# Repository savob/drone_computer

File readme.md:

# Flight Computer Project

This is the code and hardware design files for my custom flight computer board and its components.

It's been on a haitus for a while, I hope to pick it up again sometime though.

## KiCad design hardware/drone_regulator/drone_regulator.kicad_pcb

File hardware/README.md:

# Flight Computer Hardware Files

Here are the files related to the hardware design. They are all from KiCad 7.0.10 at the oldest.

## Projects

| Project | Description |
| --- | --- |
| `drone_regulator` | An noise rejecting voltage regulator board |
| `flight_computer_vX` | Different versions of the flight computer |

## Other Files and Folders

| Folder | Purpose |
| --- | --- |
| `renders` | Front and back 3D renders of the boards |
| `schematics` | Has the schematics in PDF (colour and B/W) and SVG (just colour) formats |
| `small_title_block.kicad_wks` | has the worksheet template with a more compact titleblock |

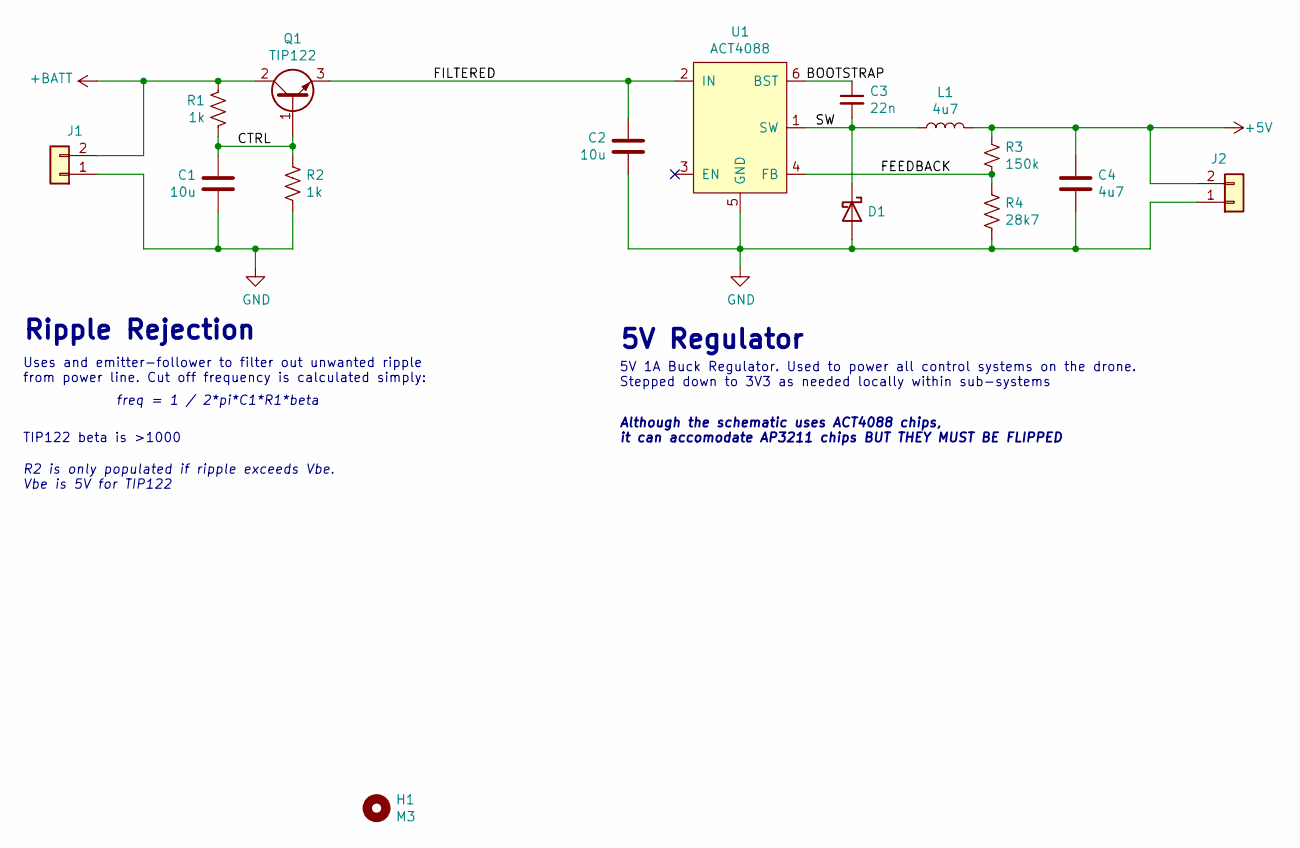
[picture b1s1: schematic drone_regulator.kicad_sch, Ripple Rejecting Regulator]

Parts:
C1: 10u; C_Radial_D6.3mm_H7.0mm_P2.50mm
C2: 10u; C_0805_2012Metric
C3: 22n; C_0402_1005Metric
C4: 4u7; C_0805_2012Metric
D1: 0v7; D_SOD-323
H1: M3; MountingHole_3.2mm_M3
J1, J2: Conn_01x02; PinHeader_1x02_P2.54mm_Vertical
L1: 4u7; L_Taiyo-Yuden_NR-30xx
Q1: TIP122; TO-220-3_Vertical
R1, R2: 1k; R_Axial_DIN0207_L6.3mm_D2.5mm_P2.54mm_Vertical
R3: 150k; R_0402_1005Metric
R4: 28k7; R_0402_1005Metric
U1: ACT4088; SOT-23-6

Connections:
+5V: C4.1, J2.2, L1.2, R3.1
+BATT: J1.2, Q1.2 (C), R1.2
/BOOTSTRAP: C3.1, U1.6 (BST)
/CTRL: C1.2, Q1.1 (B), R1.1, R2.2
/FEEDBACK: R3.2, R4.1, U1.4 (FB)
/FILTERED: C2.2, Q1.3 (E), U1.2 (IN)
/SW: C3.2, D1.1 (K), L1.1, U1.1 (SW)
GND: C1.1, C2.1, C4.2, D1.2 (A), J1.1, J2.1, R2.1, R4.2, U1.5 (GND)

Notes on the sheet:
5V 1A Buck Regulator. Used to power all control systems on the drone. Stepped down to 3V3 as needed locally within sub-systems
R2 is only populated if ripple exceeds Vbe. Vbe is 5V for TIP122
Ripple Rejection
Although the schematic uses ACT4088 chips, it can accomodate AP3211 chips BUT THEY MUST BE FLIPPED
Uses and emitter-follower to filter out unwanted ripple from power line. Cut off frequency is calculated simply: TIP122 beta is >1000
5V Regulator
freq = 1 / 2*pi*C1*R1*beta

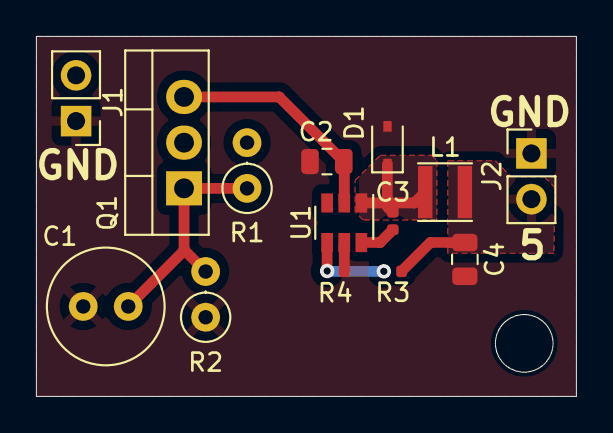
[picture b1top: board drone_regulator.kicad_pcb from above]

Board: 2 copper layers, 30.0 x 20.0 mm, 15 parts (0 on the bottom side), 8 nets.

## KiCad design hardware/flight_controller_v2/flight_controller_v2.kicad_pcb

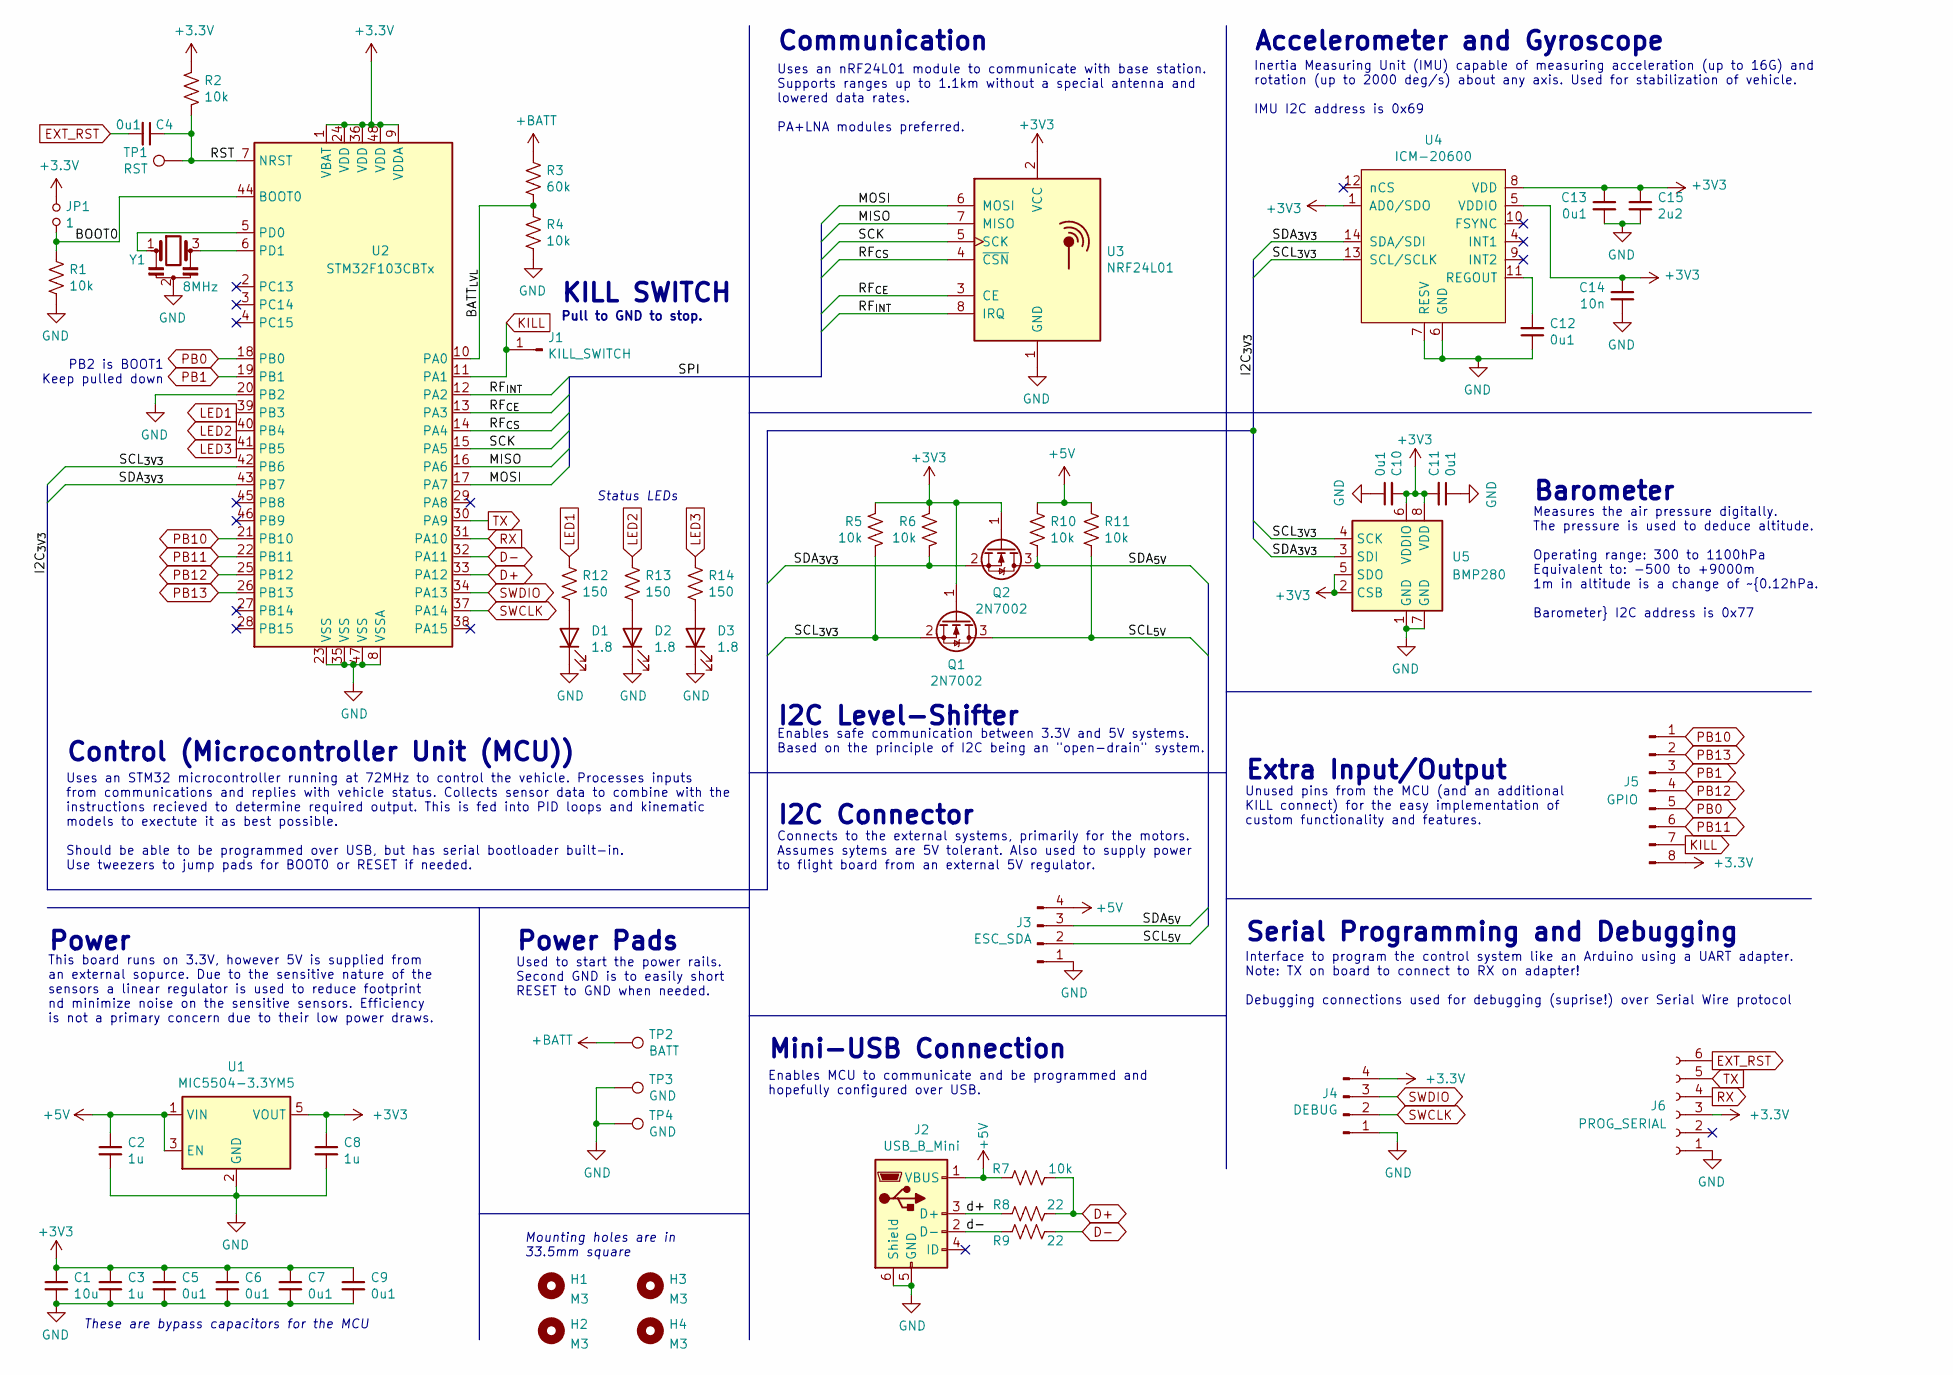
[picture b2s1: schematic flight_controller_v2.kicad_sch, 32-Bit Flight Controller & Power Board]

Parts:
C1: 10u; C_0603_1608Metric
C2, C3, C8: 1u; C_0603_1608Metric
C4, C5, C6, C7, C9, C10, C11, C12, C13: 0u1; C_0603_1608Metric
C14: 10n; C_0603_1608Metric
C15: 2u2; C_0603_1608Metric
D1, D2, D3: 1.8; LED_0805_2012Metric_Castellated
H1, H2, H3, H4: M3; MountingHole_3.2mm_M3
J1: KILL_SWITCH; PinHeader_1x01_P2.54mm_Vertical
J2: USB_B_Mini; TE_2172034-1
J3: ESC_SDA; PinHeader_1x04_P2.54mm_Vertical
J4: DEBUG; PinHeader_1x04_P2.54mm_Vertical
J5: GPIO; PinHeader_2x04_P2.00mm_Vertical_SMD
J6: PROG_SERIAL; PinSocket_1x06_P2.54mm_Vertical
JP1: 1; SolderJumper-2_P1.3mm_Open_Pad1.0x1.5mm
Q1, Q2: 2N7002; SOT-23
R1, R2, R4, R5, R6, R7, R10, R11: 10k; R_0603_1608Metric
R3: 60k; R_0603_1608Metric
R8, R9: 22; R_0603_1608Metric
R12, R13, R14: 150; R_0603_1608Metric
TP1: RST; TestPoint_Pad_1.5x1.5mm
TP2: BATT; TestPoint_Pad_4.0x4.0mm
TP3: GND; TestPoint_Pad_D2.0mm
TP4: GND; TestPoint_Pad_4.0x4.0mm
U1: MIC5504-3.3YM5; SOT-23-5
U2: STM32F103CBTx; LQFP-48_7x7mm_P0.5mm
U3: NRF24L01; nRF24L01_Breakout
U4: ICM-20600; LGA-14_3x2.5mm_P0.5mm_LayoutBorder3x4y
U5: BMP280; Bosch_LGA-8_2x2.5mm_P0.65mm_ClockwisePinNumbering
Y1: 8MHz; Resonator_SMD_muRata_CSTxExxV-3Pin_3.0x1.1mm

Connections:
+5V: C2.1, J2.1 (VBUS), J3.4, R7.1, R10.1, R11.1, U1.1 (VIN), U1.3 (EN)
+BATT: R3.1, TP2.1
/BATT_{LVL}: R3.2, R4.1, U2.10 (PA0)
/BOOT0: JP1.1, R1.1, U2.44 (BOOT0)
/MISO: U2.16 (PA6), U3.7 (MISO)
/MOSI: U2.17 (PA7), U3.6 (MOSI)
/RF_{CE}: U2.13 (PA3), U3.3 (CE)
/RF_{CS}: U2.14 (PA4), U3.4 (~CSN)
/RF_{INT}: U2.12 (PA2), U3.8 (IRQ)
/RST: C4.1, R2.2, TP1.1, U2.7 (NRST)
/SCK: U2.15 (PA5), U3.5 (SCK)
/SCL_{3V3}: Q1.2 (S), R5.2, U2.42 (PB6), U4.13 (SCL/SCLK), U5.4 (SCK)
/SCL_{5V}: J3.2, Q1.3 (D), R11.2
/SDA_{3V3}: Q2.2 (S), R6.2, U2.43 (PB7), U4.14 (SDA/SDI), U5.3 (SDI)
/SDA_{5V}: J3.3, Q2.3 (D), R10.2
/d+: J2.3 (D+), R8.2
/d-: J2.2 (D-), R9.1
D+: R7.2, R8.1, U2.33 (PA12)
D-: R9.2, U2.32 (PA11)
EXT_RST: C4.2, J6.6
GND: C1.2, C2.2, C3.2, C5.2, C6.2, C7.2, C8.2, C9.2, C10.1, C11.1, C12.1, C13.2, C14.2, C15.2, D1.1 (K), D2.1 (K), D3.1 (K), J2.5 (GND), J2.6 (Shield), J3.1, J4.1, J6.1, R1.2, R4.2, TP3.1, TP4.1, U1.2 (GND), U2.8 (VSSA), U2.20 (PB2), U2.23 (VSS), U2.35 (VSS), U2.47 (VSS), U3.1 (GND), U4.6 (GND), U4.7 (RESV), U5.1 (GND), U5.7 (GND), Y1.2
KILL: J1.1, J5.7, U2.11 (PA1)
LED1: R12.1, U2.39 (PB3)
LED2: R13.1, U2.40 (PB4)
LED3: R14.1, U2.41 (PB5)
unnamed: C12.2, U4.11 (REGOUT)
unnamed: D1.2 (A), R12.2
unnamed: D2.2 (A), R13.2
unnamed: D3.2 (A), R14.2
unnamed: U2.5 (PD0), Y1.1
unnamed: U2.6 (PD1), Y1.3
PB0: J5.5, U2.18 (PB0)
PB1: J5.3, U2.19 (PB1)
PB10: J5.1, U2.21 (PB10)
PB11: J5.6, U2.22 (PB11)
PB12: J5.4, U2.25 (PB12)
PB13: J5.2, U2.26 (PB13)
RX: J6.4, U2.31 (PA10)
SWCLK: J4.2, U2.37 (PA14)
SWDIO: J4.3, U2.34 (PA13)
TX: J6.5, U2.30 (PA9)

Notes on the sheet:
Accelerometer and Gyroscope
This board runs on 3.3V, however 5V is supplied from an external sopurce. Due to the sensitive nature of the sensors a linear regulator is used to reduce footprint nd minimize noise on the sensitive sensors. Efficiency is not a primary concern due to their low power draws.
Barometer
Power
Extra Input/Output
I2C Level-Shifter
Enables safe communication between 3.3V and 5V systems. Based on the principle of I2C being an "open-drain" system.
I2C Connector
Pull to GND to stop.
Interface to program the control system like an Arduino using a UART adapter. Note: TX on board to connect to RX on adapter! Debugging connections used for debugging (suprise!) over Serial Wire protocol
Status LEDs
Used to start the power rails. Second GND is to easily short RESET to GND when needed.
Uses an nRF24L01 module to communicate with base station. Supports ranges up to 1.1km without a special antenna and lowered data rates. PA+LNA modules preferred.
Mounting holes are in 33.5mm square
Power Pads
Control (Microcontroller Unit (MCU))
Serial Programming and Debugging
PB2 is BOOT1 Keep pulled down
Inertia Measuring Unit (IMU) capable of measuring acceleration (up to 16G) and rotation (up to 2000 deg/s) about any axis. Used for stabilization of vehicle. IMU I2C address is 0x69
Mini-USB Connection
Communication
KILL SWITCH
Uses an STM32 microcontroller running at 72MHz to control the vehicle. Processes inputs from communications and replies with vehicle status. Collects sensor data to combine with the instructions recieved to determine required output. This is fed into PID loops and kinematic models to exectute it as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
Enables MCU to communicate and be programmed and hopefully configured over USB.
Connects to the external systems, primarily for the motors. Assumes sytems are 5V tolerant. Also used to supply power to flight board from an external 5V regulator.
These are bypass capacitors for the MCU
Unused pins from the MCU (and an additional KILL connect) for the easy implementation of custom functionality and features.
Measures the air pressure digitally. The pressure is used to deduce altitude. Operating range: 300 to 1100hPa Equivalent to: -500 to +9000m 1m in altitude is a change of ~{0.12hPa. Barometer} I2C address is 0x77

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
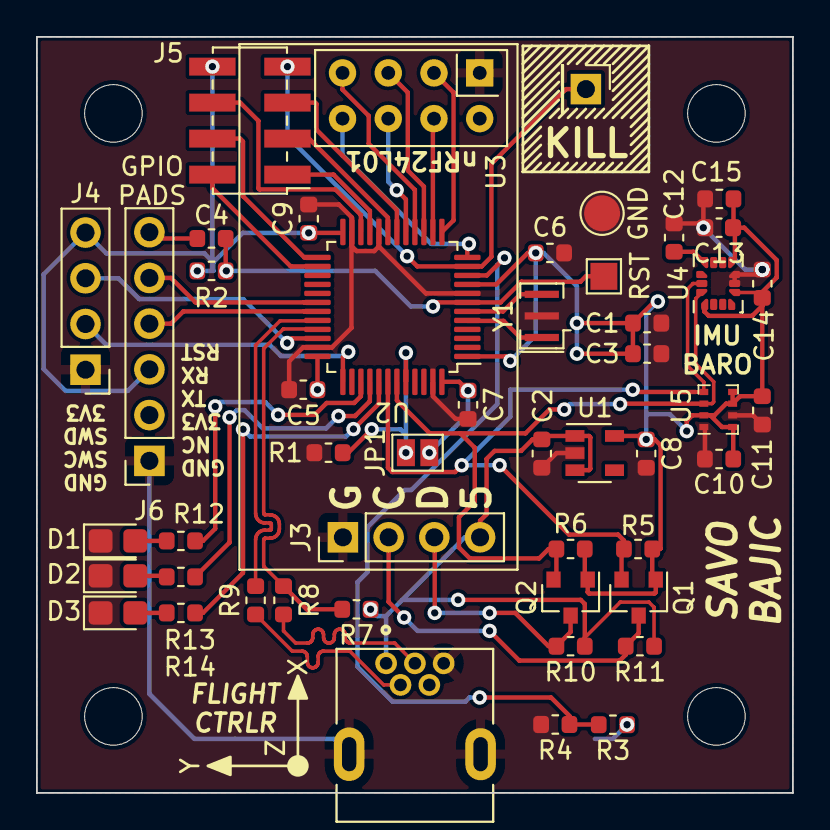
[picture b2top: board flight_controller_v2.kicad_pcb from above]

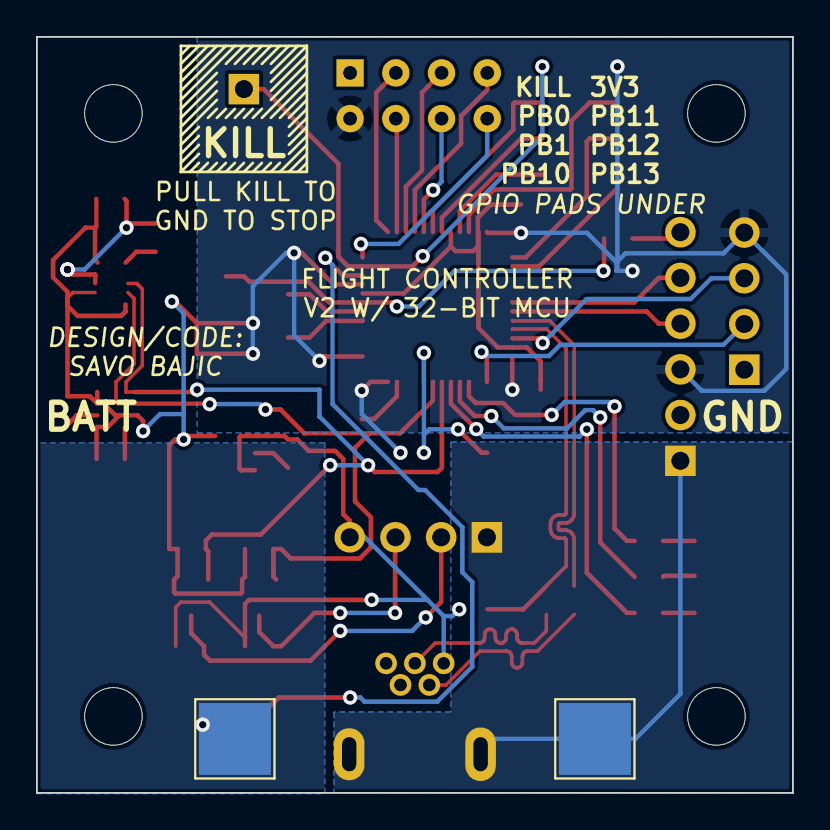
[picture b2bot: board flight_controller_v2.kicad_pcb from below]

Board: 2 copper layers, 42.0 x 42.0 mm, 55 parts (2 on the bottom side), 42 nets.

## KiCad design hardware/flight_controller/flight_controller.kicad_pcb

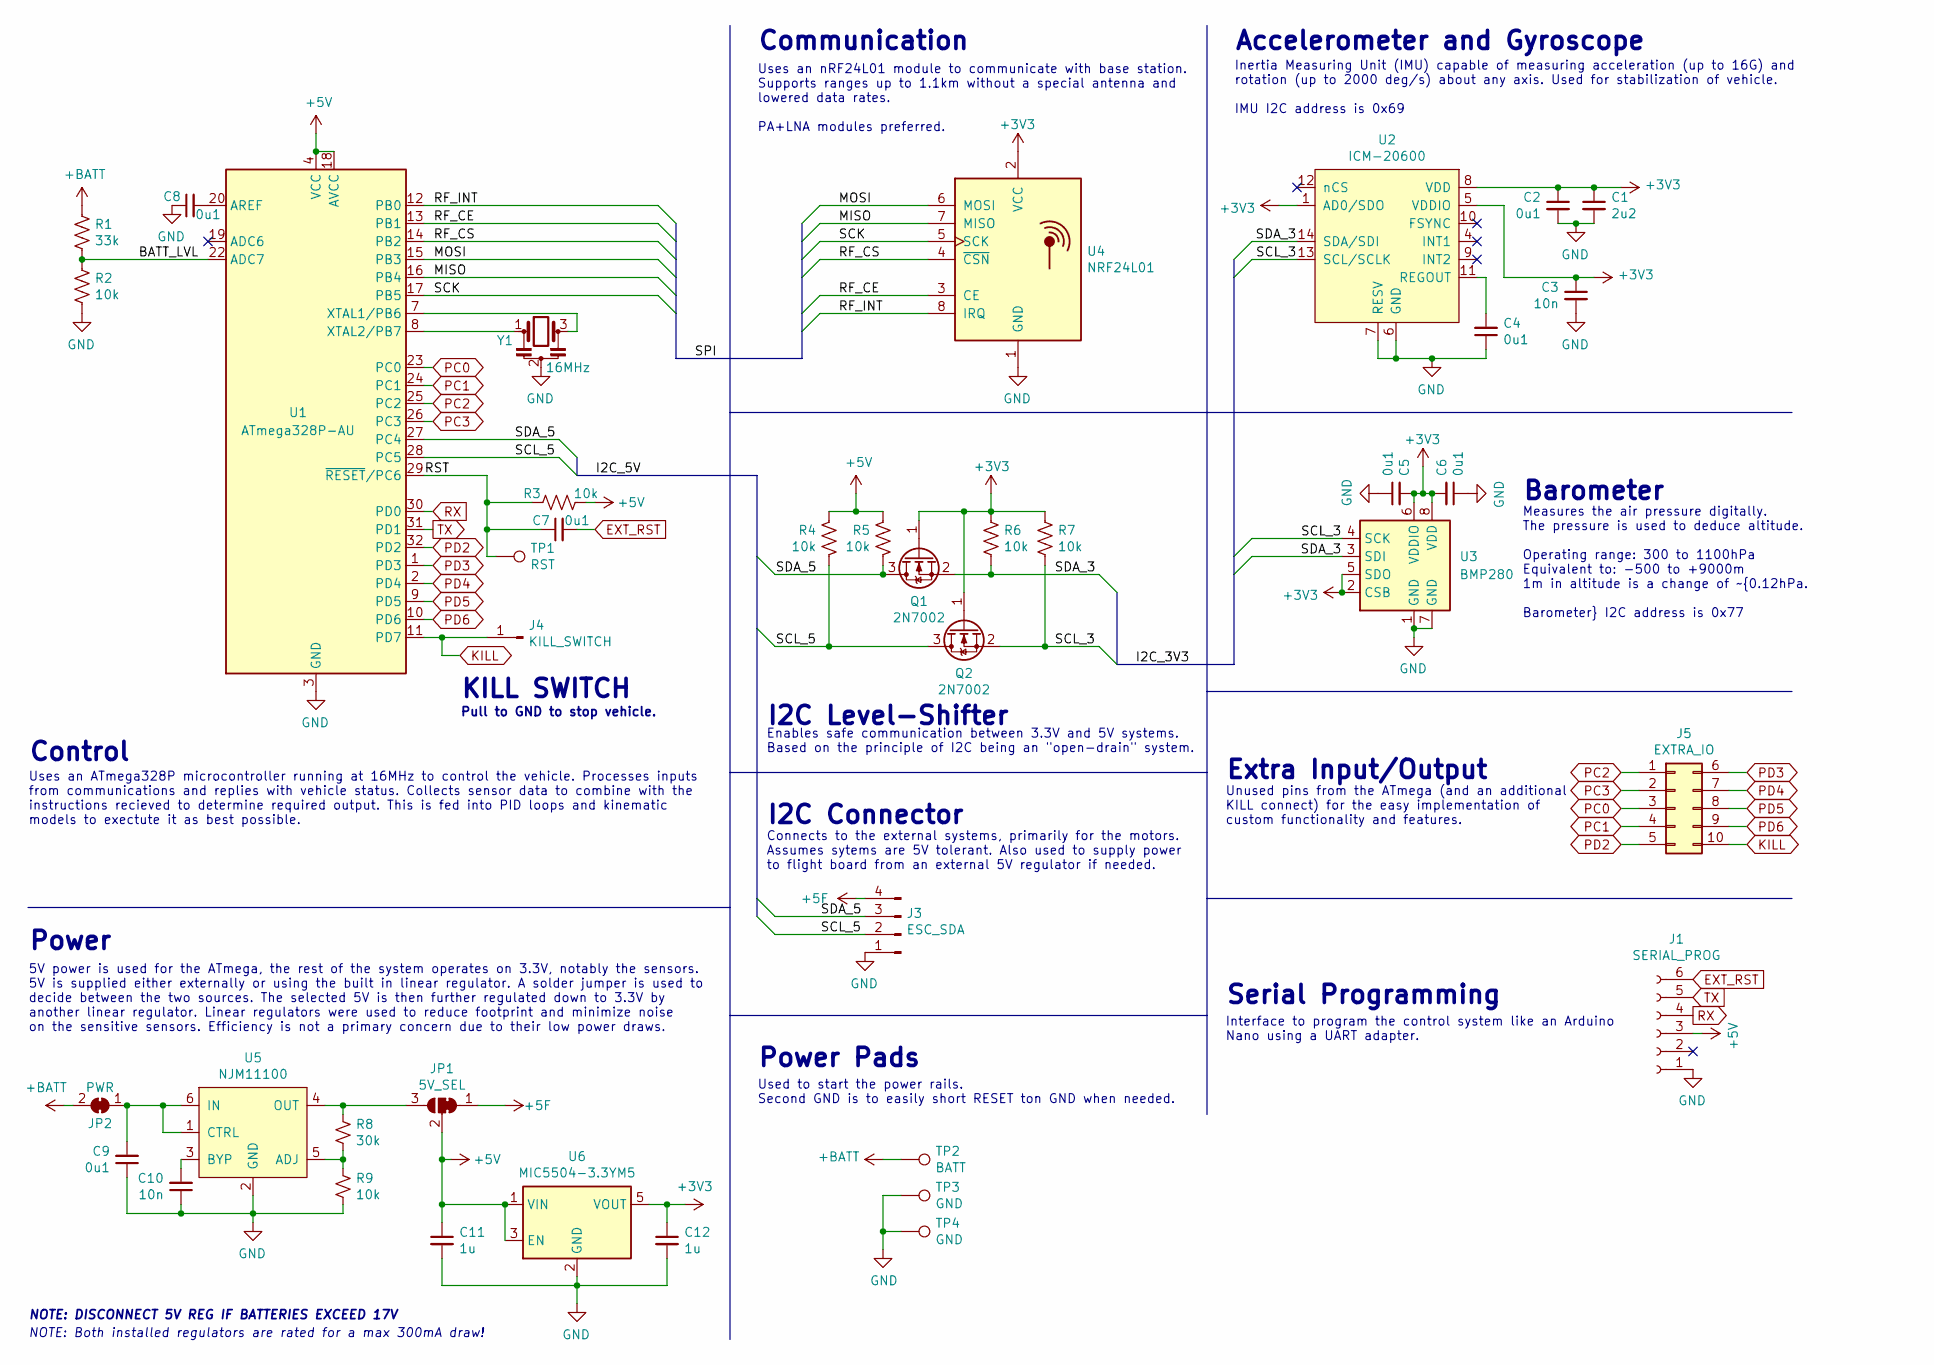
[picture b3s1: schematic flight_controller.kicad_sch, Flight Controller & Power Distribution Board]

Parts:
C1: 2u2; C_0402_1005Metric
C2, C4, C5, C6, C7, C8, C9: 0u1; C_0402_1005Metric
C3, C10: 10n; C_0402_1005Metric
C11, C12: 1u; C_0402_1005Metric
J1: SERIAL_PROG; PinSocket_1x06_P2.54mm_Vertical
J3: ESC_SDA; PinHeader_1x04_P2.54mm_Vertical
J4: KILL_SWITCH; PinHeader_1x01_P2.54mm_Vertical
J5: EXTRA_IO; PinHeader_2x05_P2.54mm_Vertical_SMD
JP1: 5V_SEL; SolderJumper-3_P2.0mm_Open_TrianglePad1.0x1.5mm
JP2: PWR; SolderJumper-2_P1.3mm_Bridged_Pad1.0x1.5mm
Q1, Q2: 2N7002; SOT-23
R1: 33k; R_0402_1005Metric
R2, R3, R4, R5, R6, R7, R9: 10k; R_0402_1005Metric
R8: 30k; R_0402_1005Metric
TP1: RST; TestPoint_Pad_1.5x1.5mm
TP2: BATT; TestPoint_Pad_4.0x4.0mm
TP3: GND; TestPoint_Pad_D2.0mm
TP4: GND; TestPoint_Pad_4.0x4.0mm
U1: ATmega328P-AU; TQFP-32_7x7mm_P0.8mm
U2: ICM-20600; LGA-14_3x2.5mm_P0.5mm_LayoutBorder3x4y
U3: BMP280; Bosch_LGA-8_2x2.5mm_P0.65mm_ClockwisePinNumbering
U4: NRF24L01; nRF24L01_Breakout
U5: NJM11100; SOT-23-6
U6: MIC5504-3.3YM5; SOT-23-5
Y1: 16MHz; Resonator_SMD_muRata_CSTxExxV-3Pin_3.0x1.1mm

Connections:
+3V3: C1.1, C2.1, C3.1, C5.2, C6.2, C12.1, Q1.1 (G), Q2.1 (G), R6.1, R7.1, U2.1 (AD0/SDO), U2.5 (VDDIO), U2.8 (VDD), U3.2 (CSB), U3.5 (SDO), U3.6 (VDDIO), U3.8 (VDD), U4.2 (VCC), U6.5 (VOUT)
+5F: J3.4, JP1.1 (A)
+5V: C11.1, J1.3, JP1.2 (C), R3.1, R4.1, R5.1, U1.4 (VCC), U1.6 (VCC), U1.18 (AVCC), U6.1 (VIN), U6.3 (EN)
+BATT: JP2.2 (B), R1.1, TP2.1
/BATT_LVL: R1.2, R2.1, U1.22 (ADC7)
/MISO: U1.16 (PB4), U4.7 (MISO)
/MOSI: U1.15 (PB3), U4.6 (MOSI)
/RF_CE: U1.13 (PB1), U4.3 (CE)
/RF_CS: U1.14 (PB2), U4.4 (~CSN)
/RF_INT: U1.12 (PB0), U4.8 (IRQ)
/RST: C7.1, R3.2, TP1.1, U1.29 (~RESET/PC6)
/SCK: U1.17 (PB5), U4.5 (SCK)
/SCL_3: Q2.2 (S), R7.2, U2.13 (SCL/SCLK), U3.4 (SCK)
/SCL_5: J3.2, Q2.3 (D), R4.2, U1.28 (PC5)
/SDA_3: Q1.2 (S), R6.2, U2.14 (SDA/SDI), U3.3 (SDI)
/SDA_5: J3.3, Q1.3 (D), R5.2, U1.27 (PC4)
EXT_RST: C7.2, J1.6
GND: C1.2, C2.2, C3.2, C4.1, C5.1, C6.1, C8.1, C9.1, C10.1, C11.2, C12.2, J1.1, J3.1, R2.2, R9.2, TP3.1, TP4.1, U1.3 (GND), U1.5 (GND), U1.21 (GND), U2.6 (GND), U2.7 (RESV), U3.1 (GND), U3.7 (GND), U4.1 (GND), U5.2 (GND), U6.2 (GND), Y1.2
KILL: J4.1, J5.10, U1.11 (PD7)
unnamed: C4.2, U2.11 (REGOUT)
unnamed: C8.2, U1.20 (AREF)
unnamed: C9.2, JP2.1 (A), U5.1 (CTRL), U5.6 (IN)
unnamed: C10.2, U5.3 (BYP)
unnamed: JP1.3 (B), R8.1, U5.4 (OUT)
unnamed: R8.2, R9.1, U5.5 (ADJ)
unnamed: U1.7 (XTAL1/PB6), Y1.3
unnamed: U1.8 (XTAL2/PB7), Y1.1
PC0: J5.3, U1.23 (PC0)
PC1: J5.4, U1.24 (PC1)
PC2: J5.1, U1.25 (PC2)
PC3: J5.2, U1.26 (PC3)
PD2: J5.5, U1.32 (PD2)
PD3: J5.6, U1.1 (PD3)
PD4: J5.7, U1.2 (PD4)
PD5: J5.8, U1.9 (PD5)
PD6: J5.9, U1.10 (PD6)
RX: J1.4, U1.30 (PD0)
TX: J1.5, U1.31 (PD1)

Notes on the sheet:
I2C Connector
Connects to the external systems, primarily for the motors. Assumes sytems are 5V tolerant. Also used to supply power to flight board from an external 5V regulator if needed.
Power
KILL SWITCH
Inertia Measuring Unit (IMU) capable of measuring acceleration (up to 16G) and rotation (up to 2000 deg/s) about any axis. Used for stabilization of vehicle. IMU I2C address is 0x69
Enables safe communication between 3.3V and 5V systems. Based on the principle of I2C being an "open-drain" system.
Extra Input/Output
Measures the air pressure digitally. The pressure is used to deduce altitude. Operating range: 300 to 1100hPa Equivalent to: -500 to +9000m 1m in altitude is a change of ~{0.12hPa. Barometer} I2C address is 0x77
Control
Interface to program the control system like an Arduino Nano using a UART adapter.
Serial Programming
Unused pins from the ATmega (and an additional KILL connect) for the easy implementation of custom functionality and features.
Communication
5V power is used for the ATmega, the rest of the system operates on 3.3V, notably the sensors. 5V is supplied either externally or using the built in linear regulator. A solder jumper is used to decide between the two sources. The selected 5V is then further regulated down to 3.3V by another linear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
Power Pads
NOTE: Both installed regulators are rated for a max 300mA draw!
Uses an ATmega328P microcontroller running at 16MHz to control the vehicle. Processes inputs from communications and replies with vehicle status. Collects sensor data to combine with the instructions recieved to determine required output. This is fed into PID loops and kinematic models to exectute 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
Uses an nRF24L01 module to communicate with base station. Supports ranges up to 1.1km without a special antenna and lowered data rates. PA+LNA modules preferred.
Accelerometer and Gyroscope
I2C Level-Shifter
NOTE: DISCONNECT 5V REG IF BATTERIES EXCEED 17V
Pull to GND to stop vehicle.
Used to start the power rails. Second GND is to easily short RESET ton GND when needed.
Barometer

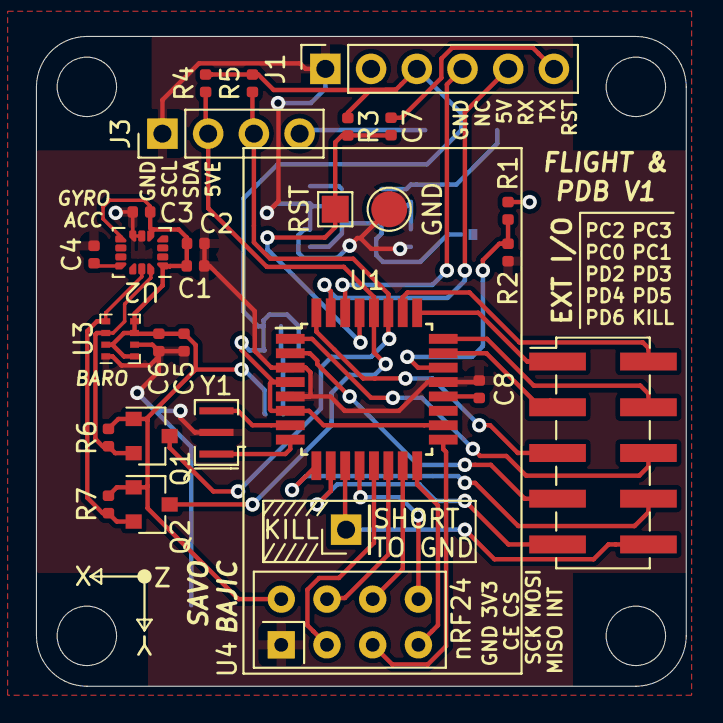
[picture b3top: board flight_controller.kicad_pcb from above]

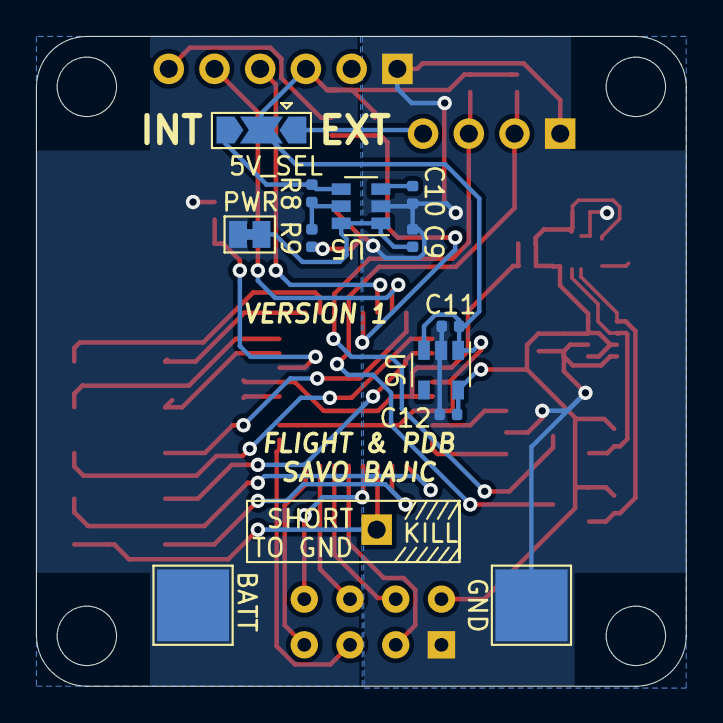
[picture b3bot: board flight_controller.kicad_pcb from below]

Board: 2 copper layers, 36.1 x 36.1 mm, 40 parts (12 on the bottom side), 38 nets.

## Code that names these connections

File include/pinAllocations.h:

/* This file contains all the GPIO pin allocations, some pins have alternate names */

#ifndef DRONE_PINS_H
#define DRONE_PINS_H

#include <Arduino.h>

// LEDs, by number and colour
const uint8_t LED1 = PB3;
const uint8_t LED2 = PB4;
const uint8_t LED3 = PB5;

const uint8_t redLED = PB3;
const uint8_t greenLED1 = PB4;
const uint8_t greenLED2 = PB5;

// KILL SWITCH
const uint8_t killPin = PA1;

// Telemetry
const uint8_t teleIntPin = PA2;
const uint8_t teleCEPin = PA3;
const uint8_t teleCSpin = PA4;

// Battery Level
const uint8_t batteryPin = PA0;
#endif

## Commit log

2021-03-08 Updated "gitignore"
2021-03-08 test
2021-03-08 Removed redundant README
2022-01-25 Updated build settings
2024-01-08 Changed USB baud variable size
2024-01-08 Upload of hardware files
2024-01-08 Moved firmware into folder
2024-01-08 Added regulator board
2024-03-20 Touchups
